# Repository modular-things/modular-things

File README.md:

# Softening Hardware with Modular-Things

use *virtualization* to easily write programs that run across multiple hardware devices

The Modular-Things project is an approach to building modular hardware systems which can be composed in software.
The underlying technology is a small networking library for packetizing and routing messages across devices ([OSAP](http://osap.tools/)) and a [web-based editor](https://modular-things.com/) for composing that hardware into functional systems in software. 

Stated simply our tools let you take hardware devices and add a library to them which allows you to plug that device into a browser-based editor where you can write programs that control it and other devices. Because it's JavaScript in the browser you can also write interfaces in HTML/CSS/JS and import various high-level libraries which interact with and control your physical computing system.

For a succinct introduction (3 min) check out our video for CHI2023 by clicking below.

An example Modular Things construction kit can be seen below with [circuits available here](https://github.com/modular-things/modular-things-circuits).

# Project Background

Modular-Things is written by [Quentin Bolsee](https://github.com/qbolsee), [Leo McElroy](https://github.com/leomcelroy) and [Jake Read](https://github.com/jakeread) based on ongoing work at the [MIT Center for Bits and Atoms](https://cba.mit.edu/) and [Hack Club](https://hackclub.com/). 

It is based on the [surprising performance of modern USB](log/2022-11_usb-motion-perf-tests-log.md), an insight that we picked up from the [urumbu project](https://gitlab.cba.mit.edu/neilg/urumbu) ([paper](https://cba.mit.edu/docs/papers/22.11.Urumbu.pdf)). Under the hood, it uses [osap](http://osap.tools/) to route packets and serialize data. Also inspired by the [virtual-machine](https://cba.mit.edu/docs/theses/16.08.Peek.pdf) architecture pioneered by [Nadya Peek](http://infosyncratic.nl/) and [Ilan Moyer](https://web.mit.edu/imoyer/www/index.html), way back in the way back. 

# Installation and Usage 

You can use the latest modular-things by navigating to [https://modular-things.com/](https://modular-things.com/), or follow these instructions to run it locally:

* install [node.js](https://nodejs.org/en/) - please use version 16.15.1 or above
* clone this repo
* run `npm install` within this repo
* run `npm run dev` to startup a local server !

### Loading Local Files

...modular-things/?file=yourFile.js&panel=devices&panelWidth=70

where file is at `repo/examples/`

--- 

# Writing New Modular-Things

For embedded (arduino) codes, install the OSAP library, which you can download as a zip here: https://github.com/jakeread/osap-arduino, and should also be available via arduino's library manager.

Also, install the `FlashStorage_SAMD` library, via the library manager.

We use the [ArduinoCore-fab-sam](https://github.com/qbolsee/ArduinoCore-fab-sam) for [these circuits](https://github.com/modular-things/modular-things-circuits), which you can install into Arduino via the notes in that repo. For the RP2040 XIAO boards, we use [Earle F. Philhower, the Third's PICO build](https://github.com/earlephilhower/arduino-pico), and for D21 XIAOs, you can follow [the XIAO docs](https://wiki.seeedstudio.com/Seeeduino-XIAO/). 

## Using the Automatic RPC

As of [`osap 0.5.0`](https://github.com/jakeread/osap-arduino/releases/tag/0.5.0), we can use an [improved design pattern](https://ekswhyzee.com/2024/02/09/no-more-newline.html) to build devices. At this time, this will only work on RP2040 based devices (which use a more modern compiler), but it is possible to back port this to c++11 based devices (most Arduinos). 

The basic pattern is pretty simple, we have a function:

```cpp
// types include float, String, int, and boolean 
float someFunction(String oneArgument, int anotherArgument){
  // ... your function body 
}
```

And we include it as a method in the devices' software object with this one-liner, handing it the function poniter, and the names of the function and its arguments: 

```cpp
OSAP_Port_RPC<decltype(&someFunction)> rpcMuleTwo(&someFunction, "someFunction", "oneArgument, anotherArgument");
```

Once we do that, and compile and load the code, the module should appear automatically when it's plugged into modular-things.com/ 

Below is a full example of a device that uses these Automatic RPCs. 

```cpp
#include <osap.h>
#include <Adafruit_GFX.h>
#include <Adafruit_SSD1306.h>

// display setup, which is wired to the XIAO's labelled SCL/SDA pins 
#define SCREEN_WIDTH 128 // OLED display width, in pixels
#define SCREEN_HEIGHT 64 // OLED display height, in pixels
#define SCREEN_ADDRESS 0x3C
Adafruit_SSD1306 display(SCREEN_WIDTH, SCREEN_HEIGHT);

// a potentiometer and a button 
// the pot is on XIAO D2/A2, which is GPIO num 28
// the button is on XIAO D3, which is GPIO num 29 (and will need a pullup)
#define PIN_POTENTIOMETER 28 
#define PIN_BUTTON 29 
#define PIN_LED_BLINK PIN_LED_R 
#define PIN_LED_WD PIN_LED_G 

// we instantiate an OSAP runtime, give it a serialport and a name: 
OSAP_Runtime osap;
OSAP_Gateway_USBSerial serLink(&Serial);
OSAP_Port_DeviceNames namePort("xylo-io-panel");

// now we want to author some functions as interfaces to our device,
// and we'll attach those as RPC's using templated OSAP_Port_RPC<> class instances 

float getPotentiometerReading(void){
  int reading = analogRead(PIN_POTENTIOMETER);
  float duty = (float)reading / 4096.0F;
  return duty; 
}

OSAP_Port_RPC<decltype(&getPotentiometerReading)> getPotRPC(&getPotentiometerReading, "getPotentiometerReading");

bool getButtonState(void){
  // we're not going to debounce anything, 
  // and our button is wired up such that it's logic high when it's not pressed, 
  // so we invert this, 
  return !(digitalRead(PIN_BUTTON));
}

OSAP_Port_RPC<decltype(&getButtonState)> rpcMuleThree(&getButtonState, "getButtonState");

uint32_t blinkOnTime = 0;

void blinkLED(void){
  // we turn an LED on and record the time, 
  // we'll check that in the loop to turn it back off, 
  // note that LEDs are wired such that logic-low is "on"
  digitalWrite(PIN_LED, LOW);
  blinkOnTime = millis();
}

OSAP_Port_RPC<decltype(&blinkLED)> rpcMuleFour(&blinkLED, "blinkLED");

void printToScreen(String message, int textSize){
  display.clearDisplay();
  display.setCursor(0, 0);
  display.setTextSize(textSize);
  display.println(message);
  display.display();
}

OSAP_Port_RPC<decltype(&printToScreen)> rpcMuleTwo(&printToScreen, "printToScreen", "message, textSize");

void newFunctionLiveDemo(int arg){
  printToScreen("you sent..." + String(arg), 3);
}

OSAP_Port_RPC<decltype(&newFunctionLiveDemo)> rpcMuleDemo(&newFunctionLiveDemo, "newFunctionLiveDemo", "intToPrint");

void setup() {
  // setup our LEDs,
  pinMode(PIN_LED_BLINK, OUTPUT);
  pinMode(PIN_LED_WD, OUTPUT);
  digitalWrite(PIN_LED_BLINK, HIGH);

  // the button needs to have a pullup
  pinMode(PIN_BUTTON, INPUT_PULLUP);
  
  // afaik, arduino sets up ADCs just by calling analogRead, 
  // and we also want to set the resolution, 
  analogReadResolution(12);
  int dummy = analogRead(PIN_POTENTIOMETER);

  // we also need to setup the display: 
  display.begin(SSD1306_SWITCHCAPVCC, SCREEN_ADDRESS);
  display.clearDisplay();
  display.display();
  display.setTextColor(SSD1306_WHITE);
  display.setTextWrap(false);

  printToScreen("bonjour", 2);

  // finally, setup OSAP,
  osap.begin();
}

const uint32_t wdInterval = 100;
uint32_t lastWd = 0;

void loop() {
  // osap runs an event loop, 
  osap.loop();

  // and we want to check in on our blinking states, 
  if(blinkOnTime){
    if(blinkOnTime + 250 < millis()){
      blinkOnTime = 0;
      digitalWrite(PIN_LED_BLINK, HIGH);
    }
  }

  // finally, we want to blink the green LED as a watchdog 
  if(lastWd + wdInterval < millis()){
    lastWd = millis();
    digitalWrite(PIN_LED_WD, !digitalRead(PIN_LED_WD));
  }
}
```

## Aligning Two Tiny Programs

To explain how module authorship works, we've just tidied up the `rgbb` example, which you can find [here (arduino)](arduino/rgbb-thing/rgbb-thing.ino) and [here (javascript)](src/lib/virtualThings/rgbb.ts).

Basically: we have an Arduino code that we give a "typeName" - that is then discovered by OSAP via the Modular-Things client. Modular-Things then looks for a matching JS or TS constructor, and if it finds one, instantiates it and passes in the devices' unique name (a string identifier). 

The constructed object can then use that string ID, as well as individual port string IDs, to route messages to its paired object. 

The result is that the "virtual thing" (javascript) acts as a proxy for the arduino-thing, making for cleaner programming model when multiple things exist in the same system. 

<table>
<tr>
  <td>
    <h2><a href="arduino/rgbb-thing/rgbb-thing.ino" target="new">Arduino "RGBB Thing"</a></h2>
  </td>
  <td>
    <h2><a href="src/lib/virtualThings/rgbb.ts" target="new">JavaScript "RGBB Thing"</a></h2>
  </td>
</tr>
<tr>
<td valign="top">

```cpp 
#include <osap.h>

// -------------------------- Define Pins for R,G and B LEDs, and one Button

#define PIN_R 14
#define PIN_G 15
#define PIN_B 16
#define PIN_BUT 17

// -------------------------- Instantiate the OSAP Runtime, 

OSAP_Runtime osap;

// -------------------------- Instantiate a link layer, 
// handing OSAP the built-in Serial object to send packetized 
// data around the network 

OSAP_Gateway_USBSerial serLink(&Serial);

// -------------------------- Adding this software-defined port 
// allows remote services to find the type-name of this device (here "rgbb")
// and to give it a unique name, that will be stored after reset 

OSAP_Port_DeviceNames namePort("rgbb");

// -------------------------- We track button state (in the loop()), 
// and we use the onButtonReq() handler (that we pass into a named port)
// to reply to messages with the provided string-name "getButtonState"

boolean lastButtonState = false;

size_t onButtonReq(uint8_t* data, size_t len, uint8_t* reply){
  // then write-into reply:
  lastButtonState ? reply[0] = 1 : reply[0] = 0;
  return 1;
}

OSAP_Port_Named getButtonState("getButtonState", onButtonReq);

// -------------------------- We can use similar structures without 
// the reply, simply recieving `data, len` on a packet to "setRGB" here 

void onRGBPacket(uint8_t* data, size_t len){
  analogWrite(PIN_R, data[0]);
  analogWrite(PIN_G, data[1]);
  analogWrite(PIN_B, data[2]);
}

OSAP_Port_Named setRGB("setRGB", onRGBPacket);

// -------------------------- Arduino Setup

void setup() {
  // startup the OSAP runtime,
  osap.begin();
  // setup our hardware... 
  analogWriteResolution(8);
  pinMode(PIN_R, OUTPUT);
  pinMode(PIN_G, OUTPUT);
  pinMode(PIN_B, OUTPUT);
  analogWrite(PIN_R, 255);
  analogWrite(PIN_G, 255);
  analogWrite(PIN_B, 255);
  // pull-down switch, high when pressed
  pinMode(PIN_BUT, INPUT);
}

// we debounce the button somewhat 

uint32_t debounceDelay = 10;
uint32_t lastButtonCheck = 0;

// -------------------------- Arduino Loop

void loop() {
  // as often as possible, we want to operate the OSAP runtime, 
  // this loop listens for messages on link-layers, and handles packets... 
  osap.loop();
  // debounce and set button states, 
  if(lastButtonCheck + debounceDelay < millis()){
    lastButtonCheck = millis();
    boolean newState = digitalRead(PIN_BUT);
    if(newState != lastButtonState){
      lastButtonState = newState;
    }
  }
}

```

</td>

<td valign="top">

```javascript
import Thing from "../../../src/lib/thing";

// the name given to us here is the "uniqueName" of the matched 
// device, we use this as a kind of address 
export default class RGBB extends Thing {
  // we can define methods that interact with the device, 
  // using the 'send' primitive, which writes data (bytes) and gets data (bytes) 
  async setRGB(r: number, g: number, b: number) {
    let datagram = new Uint8Array(3);
    datagram[0] = 255 - r * 255;
    datagram[1] = 255 - g * 255;
    datagram[2] = 255 - (b * 255) / 2;
    // to send data, we use 
    // `osap.send(name: string, targetPort: string, data: Uint8Array)`
    // ... and please use 'async' funcs with 'await' in front of 
    // network calls 
    // ... as you have probably figured out, "setRGB" here routes to 
    // the function defined around line 43 in the arduino example
    await this.send("setRGB", datagram);
  }

  async getButtonState() {
    // named-ports that return data resolve that data like-so:
    let res = await this.send("getButtonState", new Uint8Array([]));
    // and we can deserialize results... 
    if (res[0] > 0) {
      return true;
    } else {
      return false;
    }
  }

  // then we can docs our API, 
  api = [
    {
      name: "setRGB",
      args: [
        "red: 0 to 1",
        "green: 0 to 1",
        "blue: 0 to 1"
      ],
    },
    {
      name: "getButtonState",
      args: [],
      return: "0 or 1"
    }
  ]
}
```

</td>
</tr>
</table>

> At the time of writing, we mostly write modular-things using SAMD21 and RP2040 platforms. It is likely that OSAP will run on other microcontrollers, but there are funky-things that happen with Arduino's internal abstractions of i.e. `Serial` objects (which OSAP uses to button up link layers) and Flash-Storage libraries (to store names). Drop us a line if you have a favourite platform that you would like to see supported.

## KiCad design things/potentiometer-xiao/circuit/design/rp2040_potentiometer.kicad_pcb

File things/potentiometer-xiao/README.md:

---
author: Quentin Bolsee
name: accel-bno085-xiao
schematic: circuit/images/schematic.png
layout: circuit/images/layout.png
preview: circuit/images/preview.png
# fabbed: 
---

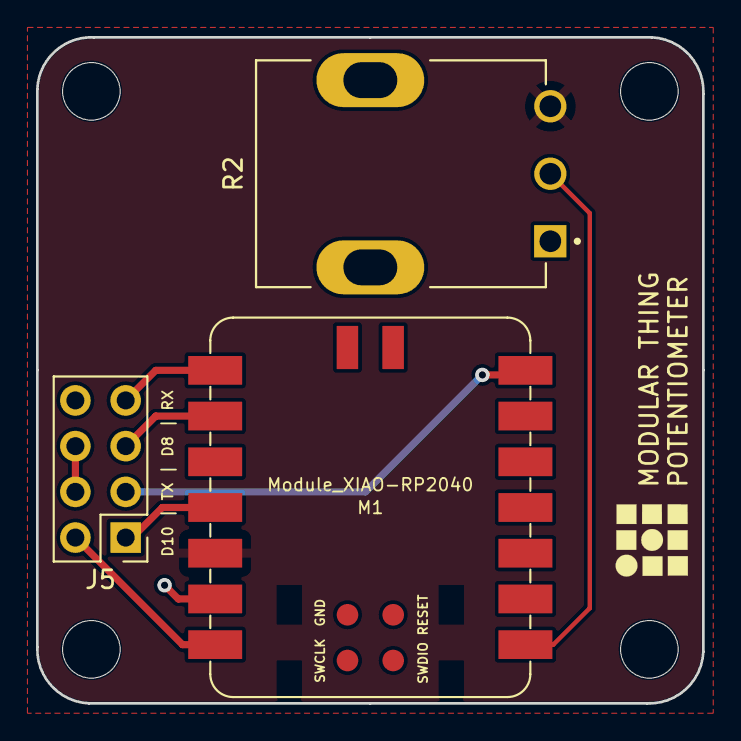
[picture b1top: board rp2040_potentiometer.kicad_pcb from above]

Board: 2 copper layers, 37.0 x 37.0 mm, 5 parts (1 on the bottom side), 8 nets.

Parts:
J5: Conn_02x04_Odd_Even; PinHeader_2x04_P2.54mm_Vertical_pinch
M1: Module_XIAO-RP2040; SeeedStudio_XIAO_RP2040_SMD
R2: P120PK-F17BR5K; TRIM_P120PK-F17BR5K
Ref**: Val**; cba_logo
Ref**#2: Val**; qr_programmer

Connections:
B_P2: J5.5, M1.9 (D8/P2)
B_P3: J5.1, M1.11 (D10/P3)
B_RX: J5.7, M1.8 (D7/P1)
B_TX: J5.3, M1.7 (D6/P0)
PWR_3V3: M1.12 (3V3), R2.3
PWR_5V: J5.2, M1.14 (5V)
PWR_GND: J5.4, J5.6, M1.13 (GND), R2.1
VAL: M1.1 (D0/P26), R2.2

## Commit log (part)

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2022-12-17 squish video
2022-12-17 last tiny editos
2022-12-17 await setname"
2022-12-18 shift some mvc codes in osapjs
2022-12-18 arduino codes for osap 0.0.1
2022-12-19 Websocket example
2022-12-19 websocket client
2022-12-20 2.30 and 34.30 fixed points in use, but needs stopDistanace up-front maths
2022-12-21 fixed point w/ no-division stopping-check calc seems OK, but accel scaling is whack
2022-12-21 scaling on internal calcs, and 2nd-order time scaling for accel vals
2023-01-04 Add start of nextjs app
2023-01-04 Add more of client functionality in client-next
2023-01-05 Implement more functionality in client-next
2023-01-05 client-next (hopefully, can't test everything) reaches feature parity with old mt-tool
2023-01-06 Add file tree
2023-01-06 Add some documentation to client-next's structure
2023-01-06 typo
2023-01-07 fix hydration error/a11y
2023-01-07 better placeholder/icon sizing
2023-01-07 Add device renaming
2023-01-07 CM tabs support + load/save state
2023-01-09 Initial webserial impl
2023-01-09 Add more webserial
2023-01-09 Modules
2023-01-09 web serial improvements
2023-01-10 Add github action for deployment
2023-01-10 move github action
2023-01-10 Set gh action working dir
2023-01-10 fix working directory for detect package manager
2023-01-10 fix upload artifact working dir
2023-01-10 fix favicon
2023-01-10 fix next setup
2023-01-12 Auto save to localstorage, help tab, font, minor improvements
2023-01-12 Fix next basepath
2023-01-12 correct bad -ve action w/ one abs()
2023-01-12 done with fixed point arithmetic
2023-01-13 Help panel, improved hooked settimeout/setinterval, full page view
2023-01-13 Add missing key shortcut
2023-01-15 xiao rp2040 PID
2023-01-25 Added more firmware
2023-02-01 init client astro
2023-02-01 WIP client-astro
2023-02-01 fixed up help markdown styles a bit
2023-02-01 removing other clients
2023-02-01 changing panel default to devices
2023-02-01 remove client directory
2023-02-01 added examples
2023-02-01 added github logo
2023-02-01 moved samples
2023-02-01 minor style changes
2023-02-01 added notes TODO and console mention in help
2023-02-01 added script bundling back in
2023-02-01 added url import example
2023-02-03 Add Web Serial API Warning
2023-02-06 added disconnect all button
2023-02-06 add redundant close calls
2023-02-10 added example machine interface
2023-02-10 added file loading
2023-02-10 added color seperation
2023-02-12 fix rgbb callback
2023-02-18 first pass at rpc, rolls up w/o arg name, osap 0.2.1
2023-02-18 add rpc code example, auto rollup works and reports APIs
2023-02-23 fix synchronizer example
2023-02-25 added thing state setter
2023-04-10 Functioning console
2023-04-18 correct pinouts on rp2040 stepper
2023-04-19 big old osap update
2023-04-19 webserial cobs link in its own box ... working on cute lil update handlers
2023-04-19 some link-insertion at old-empty-ports... and looking at upate schedules
2023-04-19 re-worked disconnect-all, learned some webserial fkery
2023-04-19 one more disconnect bug
2023-04-20 renames doubles
2023-04-20 with new rgbb... works great
2023-04-20 all the basics work, cleanup, clarifications and testing needed
2023-04-20 coupla tiny... comments ?
2023-04-20 removing deadies and re-writing names
2023-04-20 actual flowcontrol-ish in the cobs-thing
2023-04-20 updating virtual things
2023-04-20 updated things to new osap
2023-04-21 added haxidraw interface
2023-04-21 update rgbb
2023-04-21 updated firmwares
2023-04-21 new example
2023-04-21 notes on strange time-of-flight bug
2023-04-21 stepper looks good
2023-04-21 synchronizer works same-as-prior, and seems all-good with new stepper
2023-04-21 update haxidraw control
2023-04-22 match rgbb and potentiometer to osap examples
2023-04-22 author new how-to-make-new-things section
2023-04-22 table format
2023-04-22 rm sneaky h2
2023-04-22 rescan... actually rescans
2023-04-27 cleanup osapjs headers
2023-04-28 Make file url work in production
2023-04-28 Use relative paths unless in production
2023-05-10 adds checksums to name-writes, fixes shorty-names bug with osap 0.4.4
2023-05-18 fix installation and usage notes
2023-06-28 start maxl dev baby
2023-06-28 split files, embedded stub compiles
2023-06-28 embedded glue code
2023-06-29 maxl to /maxl in vt, tidy, start to test
2023-06-29 hello trajectory eating world, things are re-factored - now into queue objectification, delivery, etc
2023-06-29 add panel choice and panel width options to url
2023-06-29 ok, going to move to time-based queue mgmgt
2023-06-29 moves through a test queue OK
2023-06-29 maxl does time-estimation step
2023-06-29 barebones / dead ez halt for jogs, limits...
2023-06-30 found some dispatching bugs, fixed - two motor maxl-ing now
2023-07-01 STASH before individual-track maxl
2023-07-01 hello-world on two motors with separated position tracks
2023-07-01 chunking embedded funcking begins
2023-07-02 bust MAXL into TRAXLs
2023-07-02 decouple continues, emergency stash...
2023-07-06 working on maxl, side quest to add messageEscape debug port type
2023-07-06 ok for one test
2023-07-06 two-motor test code is OK, next steps are more track types and real config style
2023-07-15 uses config settings to subscribe, transmit, still only motion tracks though
2023-07-15 clean .gitignored-vscode arduino configs
2023-07-19 one axis home on accel demo
2023-07-19 homes and comes off OK
2023-07-19 stash b4 queue rewerk
2023-07-19 aprex fix-la the queueing bugs (we think)
2023-07-19 quick dev for pipes-up thru osap, now reading accels...
2023-07-20 finish time-sync'd accel thing, starting neopixel thing
2023-07-20 proto bitmap reader
2023-07-20 slipshod event-channel datagram authorship
2023-07-20 event track READER
2023-07-20 hello world via light painting
2023-07-26 stash with working minimal example
2023-07-26 redux for stepper motor, using memcpy deserialize
2023-07-26 lights and motion sync'd once again, a little cleaner this time
2023-08-03 roll decent pid loop on the bed heater
2023-08-08 quick haxi sketch 4 rob and leo
2023-08-08 rm console commandeering, add example rob code
2023-08-14 refactor heater code into heater-code-class
2023-08-14 bed heater and its partner are werken
2023-08-17 bed heater improves, hotend heater alive, found circuit bug in hotend-loadcell
2023-08-24 start haxiboard dev, swap maxl 'actu' to 'device' and 'reader' to 'listener'
2023-08-24 haxi board does motion things
2023-08-24 haxiboard gets a servo listener
2023-08-24 haxi proper spu, test paths
2023-08-25 add a few test files, more test paths, and do auto-scale and auto-onto-bed for svg in machine-interface
2023-08-31 sort older examples, found a bug in the transforms code
2023-08-31 maxl passes the rhino test, on the haxidraw
2023-09-06 stash before a tidy
2023-09-06 interstitial cleanup commit...
2023-09-06 ... log
2023-09-06 rename haxithing sync interf
2023-09-06 manuel merge from music-things, stashing thwappers and hubs in adhoc
2023-09-06 some cleanup and comprehension with leo
2023-09-06 rm the log
2023-09-09 expose the limit switch in the non-syncd stepper
2023-09-13 adding time-sync updates to the maxl-stepper
2023-09-24 moved things to slash-things
2023-09-24 shuffle circuits and arduino codes into things-folder
2023-09-24 template readmes
2023-11-03 add backpack spec-ish and example template
2023-11-08 towards more-better circuit docs and folder spec etc
2023-11-08 larger svg in markdown
2023-11-09 folder structure notes
2023-11-09 add dist to ignore in case of local npm-build-then-push mistake"
2023-11-09 figured some sht out
2023-11-17 add notes
2023-11-19 working on things page
2023-11-19 statically generating circuit pages
2023-11-22 tidy unstable-and-old as such
2023-11-22 cleanupt some, bring rgbb back, prep for new class...
2023-11-22 looks like new-constructor-pattern works, its free real estate
2023-11-22 tidy and note rgbb.ts example in readme
2023-11-22 touchup stepper
2023-11-22 stabilize rgbb, stepper, mosfet and servo on new inheritance
2023-11-27 start one-axis example stub
2023-11-27 peel off upgrades
2023-11-27 setup debugs and unfk schema, img for stepper
2023-11-27 new lutgen for halfwave, fill out high perf resolution for steppage
2023-11-27 spacing in servo.ts and fixed-p stepper_point
2023-11-27 cleanup!
2023-11-28 resolve fixed point and multi-tick commutation, no guards on FP overflows yet
2023-11-28 added guards on fixedp arithmetic
2023-11-28 use fixedp64 to avoid position overflows
2023-11-28 reconfig _global
2023-11-28 fixed point position, vel modes should work, testing next
2023-11-29 sys tests OK
2023-11-29 cleanup, tests still OK
2023-11-29 re-interfaced
2023-11-29 stabilize motor fw, one dof limit example is OK
2023-11-29 sync to match motors, motion-upgrades complete
2023-11-29 unfk-d some API notes for moteur
2023-11-30 rename things for gallery WIP
2023-11-30 things gallery
2023-11-30 add links to images
2023-11-30 added code snippets
2023-11-30 firmware progress
2023-12-01 apres machine-week-recitation-two
2023-12-01 xiao firmware
2023-12-01 todo notes
2023-12-01 tidy TODO
2023-12-01 tidy _things.json, flatten unstable-things
2023-12-01 cleanup /things menus, links, etc
2023-12-01 rel href fkery
2023-12-01 thing page title
2023-12-03 servo fix
2023-12-06 velocity-near-zero statemachine bug fix
2023-12-12 small note on URL args
2024-02-05 just some todos
2024-02-05 proto rpc port
2024-02-05 tuple candidate
2024-02-06 towards that rpc... starting in on js caller impl
2024-02-07 candidate working auto-rpc, missing lots of handles and maybe stack overflowing
2024-02-08 rollup OK on one function, one mule...
2024-02-08 can compile now across ret-args, void-args, ret-void, and void-void functions
2024-02-09 mostly done specializing etc for void-void, void-args, ret-args, ret-void etc, just need to specialize constructor
2024-02-09 no-args cpp constructor defers to main, and some tidy in ts
2024-02-10 it's the xylo-panel example, yall
2024-02-13 state after recording osap 0.5.0 update
2024-02-13 modify the readme for the auto RPC
2024-02-13 try move to modular-things.com
2024-02-20 try to fix slash-things rel link
